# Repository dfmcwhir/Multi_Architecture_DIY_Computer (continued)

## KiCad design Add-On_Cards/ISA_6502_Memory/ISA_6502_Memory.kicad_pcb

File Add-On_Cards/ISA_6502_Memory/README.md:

# <h2> 6502 Memory expansion card</h2>
<p>New card that hasn't been built or tested yet. It is currently only planned to be used with the 6502_CPU_Rev2 card. It is possible that in the future other CPU cards can be adapted to use this card as well. When I designed this card, I went for maximum RAM, so consequently it has 16 banks of RAM and only the one bank of ROM selectable by the CPU. My thinking was that I have mass storage options for permanent storage, so I didn't need more ROM. That maybe fine, but I kind of wish I had designed it with more flexibility in mind. Maybe that will for the next revision. Maybe I want to add ROM banks for a cartridge like system for instance. </p>

<p>To enable the memory card the address decoding PLD on the 6502_CPU_Rev2 needs to disable the on-board ROM and RAM (which in the PLD file means commenting out "Block A") and enabling the external memory card (which means uncommenting out "Block B" in the PLD file).</p>

<h2> Populating the memory card</h2>
<p>There is one socket for RAM that can be set via a jumper JP1 to be either an AS6C1008 or AS6C4008 chip. There are 2 ROM sockets for flexibility, but only one can be populated. Socket 2 (32pins), can be a SST39SF010 OR a OneROM can be put in socket 3 (28pins). The OneROM can be configured as either a 27512 (JP3 pins 1-2) or a 23C1000 (JP3 pins 2-3). A 27512 (and possibly other 28 pin ROMs) could also be used in the OneROM socket. The important thing to remember is that only one of the 2 sockets can be populated. Regardless of the which socket or what type of chip is used, only 32K of the ROM will be addressable by the CPU.</p>

<h2> RAM Bank Selection</h2>
<p>The card’s RAM range $0000–$7EFF is split in two:

* $0000–$0FFF: fixed. It’s always bank 0 of the RAM chip, whatever bank is selected, so zero page, the stack and the BIOS variables never disappear.
* $1000–$7EFF: the banked window (about 28K). Which bank you see is set by the bank register.

The bank register sits on the CPU board, in the interrupt GAL at $7FFE. Writing a value 0–15 there puts it on bus lines BA16–BA19. The card’s GAL passes those bits to the RAM chip’s top address lines (RA15–RA18), but only while the address is in the window. In the fixed area it forces them to 0.

Each bank is a 32K slice of the RAM chip: physical address = bank × $8000 + CPU address.

* AS6C4008 (512K): 16 banks (JP1 2–3).
* AS6C1008 (128K): 4 banks (JP1 1–2).

The $0000–$0FFF part of every slice except bank 0 is simply never reached. That’s the price of keeping the address calculation simple. </p>

<h2> Manual ROM bank selection </h2>
<p>The CPU can't select ROM banks, but different banks can be selected manually using jumpers. On the card, JP4 and JP5 choose which 32K image of the ROM chip appears at $8000–$FFFF. A 27SF512-style OneROM image holds 2 of them; the SST39SF010A and the MX23C1000 hold 4. Theoretically we could enable CPU switching of ROM banks by using bodge wires from JP4 and JP5 to the unused pins on the PLD and reprograming the PLD to use BA18-19 to control the ROM bank switching lines we added (RO15-16) instead of RA17-18. That would give us 4 banks of CPU switchable ROM at the expense of reducing us to 4 banks of RAM.</p>

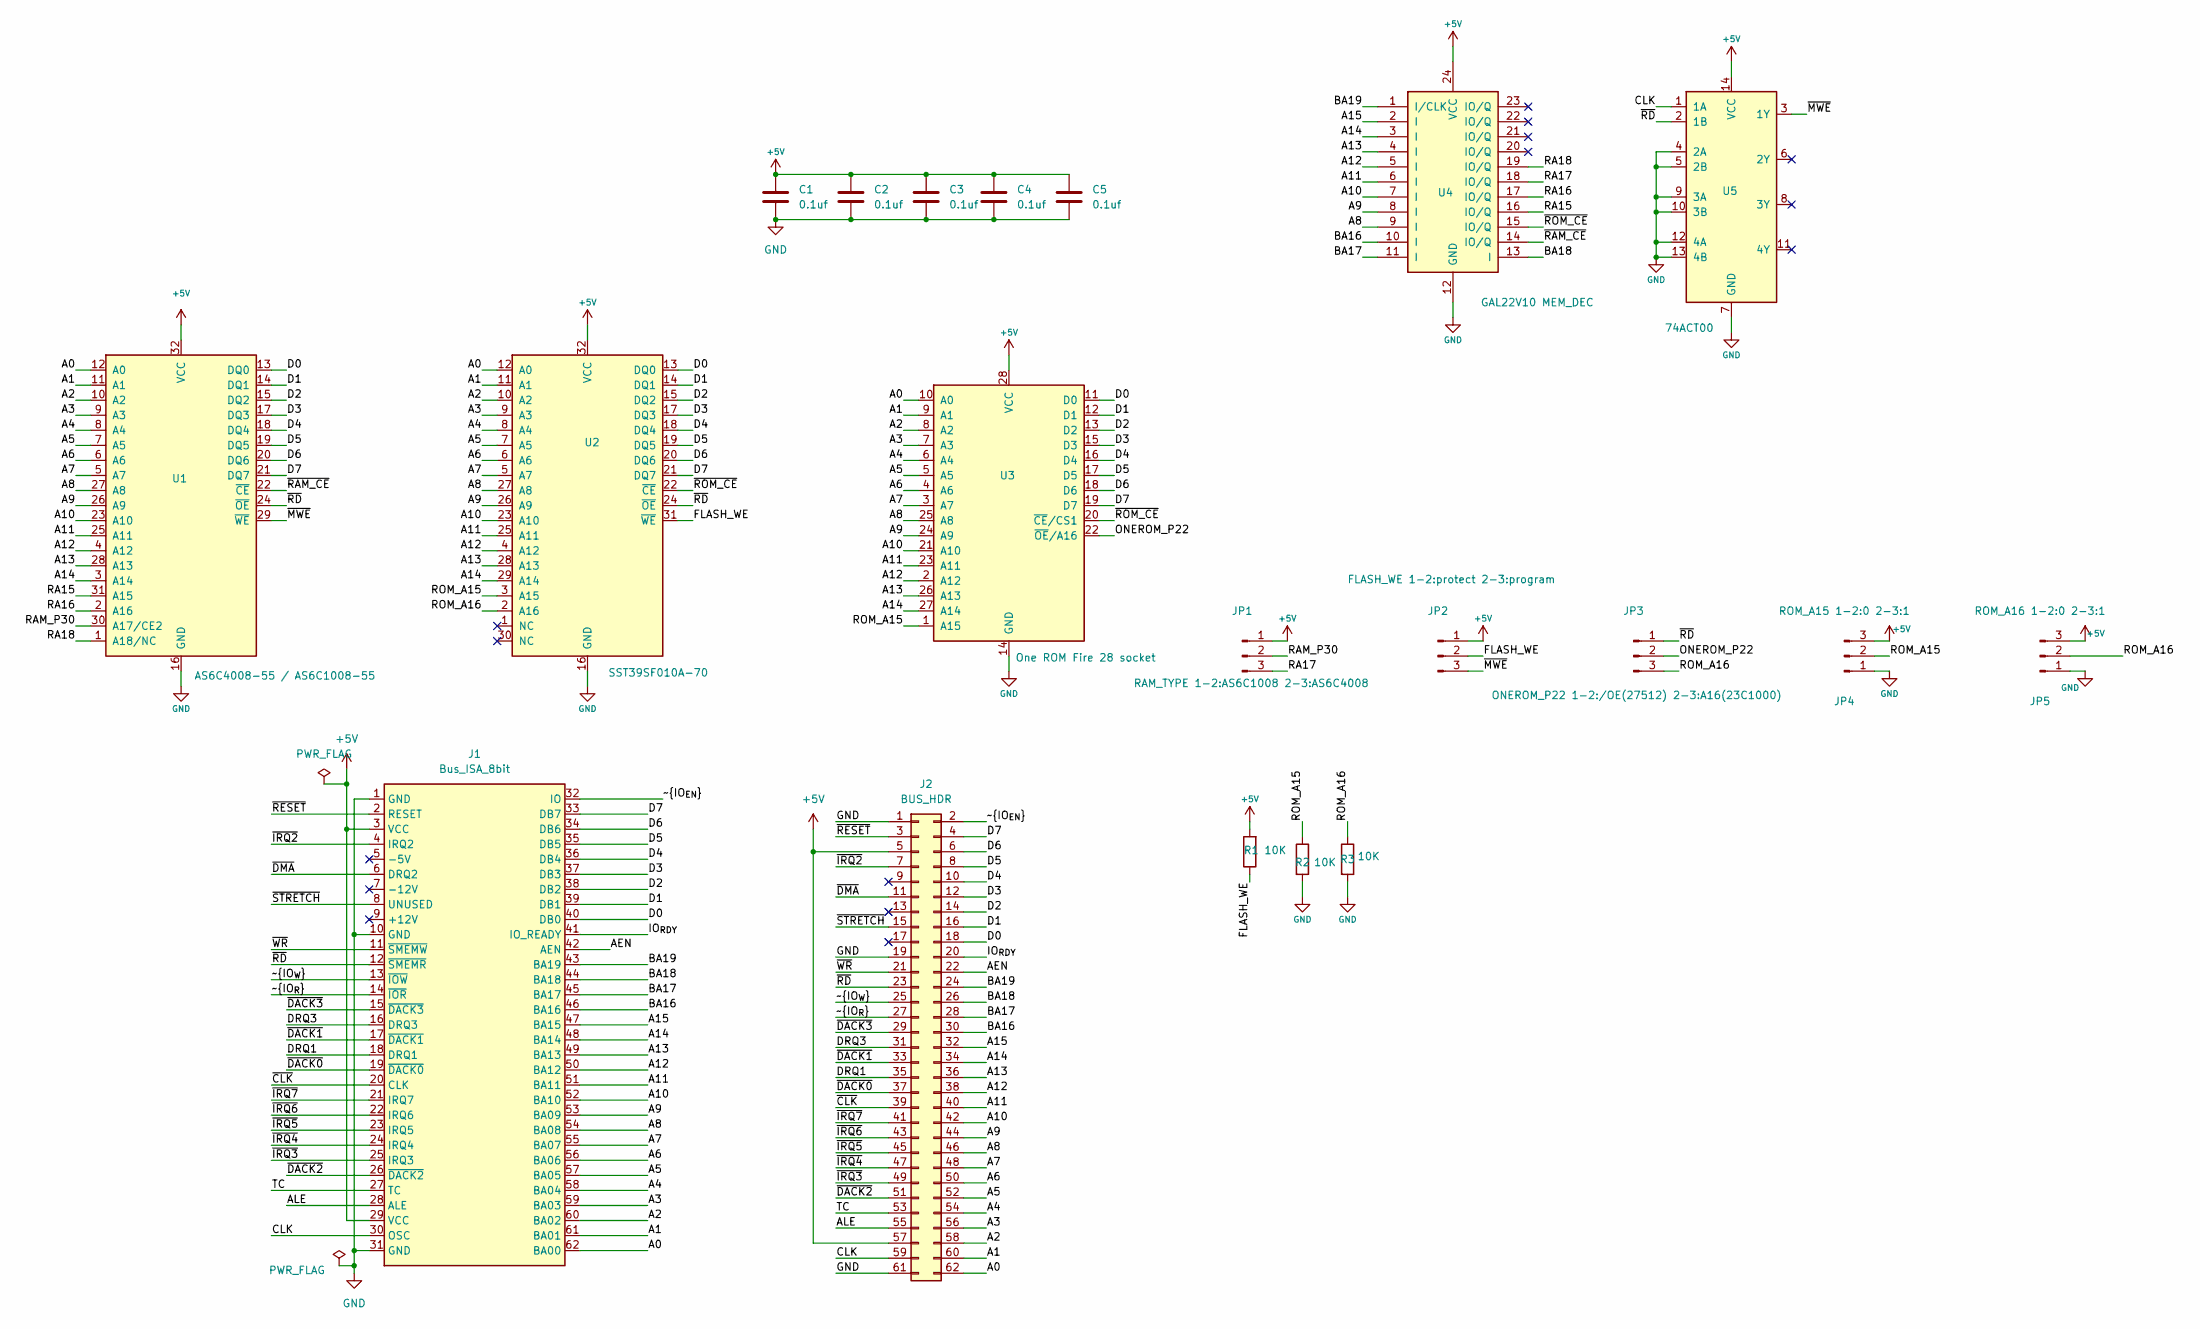
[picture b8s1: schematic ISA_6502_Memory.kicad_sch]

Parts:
C1, C2, C3, C4, C5: 0.1uf; C_Disc_D4.7mm_W2.5mm_P5.00mm
J1: Bus_ISA_8bit; BUS_8-bit_ISA
J2: BUS_HDR; PinHeader_2x31_P2.54mm_Vertical
JP1: RAM_TYPE 1-2:AS6C1008 2-3:AS6C4008; PinHeader_1x03_P2.54mm_Vertical
JP2: FLASH_WE 1-2:protect 2-3:program; PinHeader_1x03_P2.54mm_Vertical
JP3: ONEROM_P22 1-2:/OE(27512) 2-3:A16(23C1000); PinHeader_1x03_P2.54mm_Vertical
JP4: ROM_A15 1-2:0 2-3:1; PinHeader_1x03_P2.54mm_Vertical
JP5: ROM_A16 1-2:0 2-3:1; PinHeader_1x03_P2.54mm_Vertical
R1, R2, R3: 10K; R_Axial_DIN0207_L6.3mm_D2.5mm_P10.16mm_Horizontal
U1: AS6C4008-55 / AS6C1008-55; DIP-32_W15.24mm_Socket
U2: SST39SF010A-70; DIP-32_W15.24mm_Socket
U3: One ROM Fire 28 socket; DIP-28_W15.24mm_Socket
U4: GAL22V10 MEM_DEC; DIP-24_W7.62mm
U5: 74ACT00; DIP-14_W7.62mm

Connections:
+5V: C1.1, C2.1, C3.1, C4.1, C5.1, J1.3 (VCC), J1.29 (VCC), J2.5, J2.57, JP1.1, JP2.1, JP4.3, JP5.3, R1.2, U1.32 (VCC), U2.32 (VCC), U3.28 (VCC), U4.24 (VCC), U5.14 (VCC)
/A0: J1.62 (BA00), J2.62, U1.12 (A0), U2.12 (A0), U3.10 (A0)
/A1: J1.61 (BA01), J2.60, U1.11 (A1), U2.11 (A1), U3.9 (A1)
/A2: J1.60 (BA02), J2.58, U1.10 (A2), U2.10 (A2), U3.8 (A2)
/A3: J1.59 (BA03), J2.56, U1.9 (A3), U2.9 (A3), U3.7 (A3)
/A4: J1.58 (BA04), J2.54, U1.8 (A4), U2.8 (A4), U3.6 (A4)
/A5: J1.57 (BA05), J2.52, U1.7 (A5), U2.7 (A5), U3.5 (A5)
/A6: J1.56 (BA06), J2.50, U1.6 (A6), U2.6 (A6), U3.4 (A6)
/A7: J1.55 (BA07), J2.48, U1.5 (A7), U2.5 (A7), U3.3 (A7)
/A8: J1.54 (BA08), J2.46, U1.27 (A8), U2.27 (A8), U3.25 (A8), U4.9 (I)
/A9: J1.53 (BA09), J2.44, U1.26 (A9), U2.26 (A9), U3.24 (A9), U4.8 (I)
/A10: J1.52 (BA10), J2.42, U1.23 (A10), U2.23 (A10), U3.21 (A10), U4.7 (I)
/A11: J1.51 (BA11), J2.40, U1.25 (A11), U2.25 (A11), U3.23 (A11), U4.6 (I)
/A12: J1.50 (BA12), J2.38, U1.4 (A12), U2.4 (A12), U3.2 (A12), U4.5 (I)
/A13: J1.49 (BA13), J2.36, U1.28 (A13), U2.28 (A13), U3.26 (A13), U4.4 (I)
/A14: J1.48 (BA14), J2.34, U1.3 (A14), U2.29 (A14), U3.27 (A14), U4.3 (I)
/A15: J1.47 (BA15), J2.32, U4.2 (I)
/AEN: J1.42 (AEN), J2.22
/ALE: J1.28 (ALE), J2.55
/BA16: J1.46 (BA16), J2.30, U4.10 (I)
/BA17: J1.45 (BA17), J2.28, U4.11 (I)
/BA18: J1.44 (BA18), J2.26, U4.13 (I)
/BA19: J1.43 (BA19), J2.24, U4.1 (I/CLK)
/CLK: J1.30 (OSC), J2.59, U5.1 (1A)
/D0: J1.40 (DB0), J2.18, U1.13 (DQ0), U2.13 (DQ0), U3.11 (D0)
/D1: J1.39 (DB1), J2.16, U1.14 (DQ1), U2.14 (DQ1), U3.12 (D1)
/D2: J1.38 (DB2), J2.14, U1.15 (DQ2), U2.15 (DQ2), U3.13 (D2)
/D3: J1.37 (DB3), J2.12, U1.17 (DQ3), U2.17 (DQ3), U3.15 (D3)
/D4: J1.36 (DB4), J2.10, U1.18 (DQ4), U2.18 (DQ4), U3.16 (D4)
/D5: J1.35 (DB5), J2.8, U1.19 (DQ5), U2.19 (DQ5), U3.17 (D5)
/D6: J1.34 (DB6), J2.6, U1.20 (DQ6), U2.20 (DQ6), U3.18 (D6)
/D7: J1.33 (DB7), J2.4, U1.21 (DQ7), U2.21 (DQ7), U3.19 (D7)
/DRQ1: J1.18 (DRQ1), J2.35
/DRQ3: J1.16 (DRQ3), J2.31
/FLASH_WE: JP2.2, R1.1, U2.31 (~WE)
/IO_{RDY}: J1.41 (IO_READY), J2.20
/ONEROM_P22: JP3.2, U3.22 (~OE/A16)
/RA15: U1.31 (A15), U4.16 (IO/Q)
/RA16: U1.2 (A16), U4.17 (IO/Q)
/RA17: JP1.3, U4.18 (IO/Q)
/RA18: U1.1 (A18/NC), U4.19 (IO/Q)
/RAM_P30: JP1.2, U1.30 (A17/CE2)
/ROM_A15: JP4.2, R2.1, U2.3 (A15), U3.1 (A15)
/ROM_A16: JP3.3, JP5.2, R3.1, U2.2 (A16)
/TC: J1.27 (TC), J2.53
/~CLK: J1.20 (CLK), J2.39
/~DACK0: J1.19 (~DACK0), J2.37
/~DACK1: J1.17 (~DACK1), J2.33
/~DACK2: J1.26 (~DACK2), J2.51
/~DACK3: J1.15 (~DACK3), J2.29
/~DMA: J1.6 (DRQ2), J2.11
/~IO_{EN}: J1.32 (IO), J2.2
/~IO_{R}: J1.14 (~IOR), J2.27
/~IO_{W}: J1.13 (~IOW), J2.25
/~IRQ2: J1.4 (IRQ2), J2.7
/~IRQ3: J1.25 (IRQ3), J2.49
/~IRQ4: J1.24 (IRQ4), J2.47
/~IRQ5: J1.23 (IRQ5), J2.45
/~IRQ6: J1.22 (IRQ6), J2.43
/~IRQ7: J1.21 (IRQ7), J2.41
/~MWE: JP2.3, U1.29 (~WE), U5.3 (1Y)
/~RAM_CE: U1.22 (~CE), U4.14 (IO/Q)
/~RD: J1.12 (~SMEMR), J2.23, JP3.1, U1.24 (~OE), U2.24 (~OE), U5.2 (1B)
/~RESET: J1.2 (RESET), J2.3
/~ROM_CE: U2.22 (~CE), U3.20 (~CE/CS1), U4.15 (IO/Q)
/~STRETCH: J1.8 (UNUSED), J2.15
/~WR: J1.11 (~SMEMW), J2.21
GND: C1.2, C2.2, C3.2, C4.2, C5.2, J1.1 (GND), J1.10 (GND), J1.31 (GND), J2.1, J2.19, J2.61, JP4.1, JP5.1, R2.2, R3.2, U1.16 (GND), U2.16 (GND), U3.14 (GND), U4.12 (GND), U5.4 (2A), U5.5 (2B), U5.7 (GND), U5.9 (3A), U5.10 (3B), U5.12 (4A), U5.13 (4B)

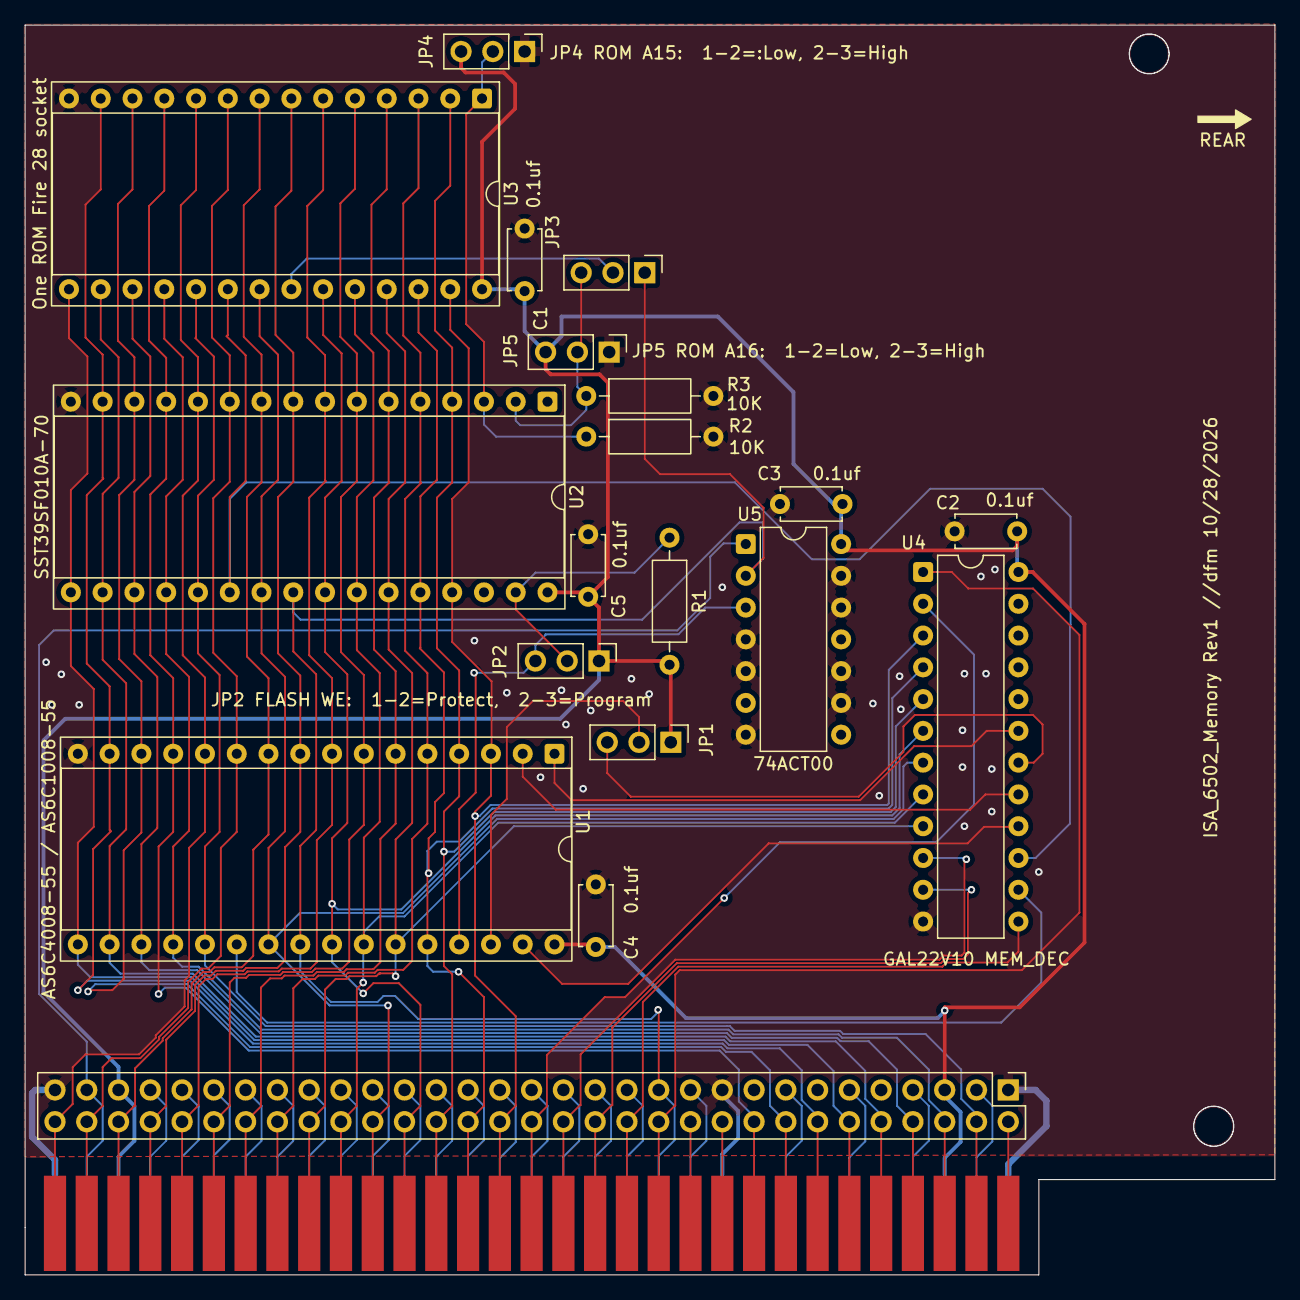
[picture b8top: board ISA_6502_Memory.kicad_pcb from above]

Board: 2 copper layers, 99.9 x 99.9 mm, 20 parts (0 on the bottom side), 68 nets.

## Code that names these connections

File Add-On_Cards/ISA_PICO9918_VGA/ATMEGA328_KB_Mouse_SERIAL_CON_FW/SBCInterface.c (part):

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// The display output of the original (8-bit, 4-bit and TWI display links and
// the ANSI interpreter) has been removed - the PICO9918 is the display now.
//
// Version 2: adds a PS/2 mouse on PC4 (clock) and PC0 (data).
//
// What it does
// ------------
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//
// ATmega328P pin use (DIP-28, 11.0592 MHz crystal)
// ------------------------------------------------
//   PB0-PB5  AVR bus D0-D5  (to '573 D inputs and '574 Q outputs)
//   PD6-PD7  AVR bus D6-D7
//   PB6-PB7  crystal
//   PC0      MOUSE DATA  (pull-up 4.7k-10k)   - was the optional /CTS input
//   PC1      KB clock    (pull-up)
//   PC2      KB data     (pull-up)
//   PC3      /RTS out
//   PC4      MOUSE CLOCK (pull-up 4.7k-10k)
//   PC5      KBAVAIL out -> GAL pin 14   (10k pull-down)
//   PC6      /RESET - keep it as reset (using it as I/O needs the RSTDISBL
//            fuse, which stops ISP programming)
//   PD0      RXD
//   PD1      TXD
//   PD2      INT0 <- /KBRD (GAL pin 17)  - byte acknowledge
//   PD3      <- DBUSY (GAL pin 22)       - 6502 has written a TX byte
//   PD4      /DOE  -> '574 /OE and GAL pin 23 (10k pull-up)
//   PD5      LE    -> '573 LE (10k pull-down)
//
// Handshakes
// ----------
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#include <stdint.h>

// ---------------------------------------------------------------- pins
#define KBAVAIL_BIT  PC5
#define RTS_BIT      PC3
#define KB_CLK_BIT   PC1
#define KB_DATA_BIT  PC2
#define MS_CLK_BIT   PC4
#define MS_DATA_BIT  PC0
#define DBUSY_BIT    PD3
#define DOE_BIT      PD4
#define LE_BIT       PD5

#define BUS_B_MASK   0x3F   // PB0-PB5 = D0-D5
#define BUS_D_MASK   0xC0   // PD6-PD7 = D6-D7

// ---------------------------------------------------------------- PS/2 devices
typedef struct
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		}
		else
		{
			d->writeActive = 0;                 // 11: device ack bit
			d->bitCount = 0;
			d->shift = 0;
		}
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	}
}

// Keyboard clock (PC1) and mouse clock (PC4) both raise PCINT1
ISR(PCINT1_vect)
{
	uint8_t pinc = PINC;
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	hostIn = hostOut = 0;
	txIn = txOut = 0;

	// AVR bus: inputs, no pull-ups (PB6/PB7 are the crystal)
	DDRB = 0x00;
	PORTB = 0x00;

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
	// Port D: /DOE high (set before enabling the output), LE low,
	// pull-up on the /KBRD input
	PORTD = (1 << DOE_BIT) | (1 << PD2);
	DDRD = (1 << PD1) | (1 << DOE_BIT) | (1 << LE_BIT);

	// Clear any DBUSY left set at power-up: hold /DOE low for a few clocks
	PORTD &= ~(1 << DOE_BIT);
	_delay_us(20);
	PORTD |= (1 << DOE_BIT);

	// PS/2 clocks: PC1 (keyboard) and PC4 (mouse) pin-change interrupts
	lastPinC = PINC;
	PCICR = 1 << PCIE1;
	PCMSK1 = (1 << PCINT9) | (1 << PCINT12);

	// INT0 (PD2, /KBRD) on rising edge = end of the 6502's read
	EICRA = (1 << ISC01) | (1 << ISC00);
	EIFR = 1 << INTF0;
	EIMSK = 1 << INT0;
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
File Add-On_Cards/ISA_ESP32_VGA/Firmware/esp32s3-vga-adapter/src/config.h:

// ESP32-S3 VGA / keyboard / mouse / sound adapter for a W65C02S computer.
// Pin map and build-time configuration.
//
// Board: ESP32-S3-DevKitC-1 (WROOM-1 N16R8 or N8R2 etc.). GPIO 33-37 are left
// free because octal-PSRAM modules use them. GPIO 19/20 are the native USB
// pins (USB host for keyboard/mouse). GPIO 43/44 stay as UART0 for upload and
// debug through the board's "UART" USB port.
#pragma once
#include <stdint.h>

// ---------------------------------------------------------------- 6502 bus
// All bus pins must be < 32 so one read of GPIO_IN_REG captures everything.
// D0..D7 must be consecutive GPIOs starting at PIN_D0.
#define PIN_D0        4     // D0..D7 = GPIO4..GPIO11 (via 74LVC8T245)
#define PIN_A0        12    // register select bit 0   (from GAL, open drain + 1k pull-up)
#define PIN_A1        13    // register select bit 1   (input)
#define PIN_RW        14    // R/W from CPU, 1 = read  (input)
#define PIN_NCS       15    // /CS for $7F18-$7F1B, decoded by the GAL, active low
#define PIN_PHI2      16    // PHI2 clock (input)
#define PIN_ACK       17    // to GAL ACK: 0 = hold RDY low while selected
#define PIN_IRQ       18    // to GAL IRQREQ: 1 = pull /IRQ low

// ---------------------------------------------------------------- VGA
// 2-bit-per-channel resistor DAC like FabGL (64 colours).
// Pixel byte format: 0b00RRGGBB.
#define PIN_VGA_B0    46
#define PIN_VGA_B1    45
#define PIN_VGA_G0    48
#define PIN_VGA_G1    47
#define PIN_VGA_R0    42
#define PIN_VGA_R1    41
#define PIN_VGA_HSYNC 39
#define PIN_VGA_VSYNC 40

// ---------------------------------------------------------------- PS/2
// Through a BSS138 4-channel bidirectional level shifter (5 V <-> 3.3 V).
#define PIN_KBD_CLK   1
#define PIN_KBD_DAT   2
#define PIN_MOUSE_CLK 21
#define PIN_MOUSE_DAT 3

// ---------------------------------------------------------------- Audio
// Sigma-delta output -> RC low-pass filter -> amplifier / line out.
#define PIN_AUDIO     38

// ---------------------------------------------------------------- Video timing
// 640x480 @ 60 Hz industry standard timing, negative sync polarity.
#define VGA_PCLK_HZ   25175000
#define VGA_H_RES     640
#define VGA_V_RES     480
#define VGA_HFP       16
#define VGA_HSYNC     96
#define VGA_HBP       48
#define VGA_VFP       10
#define VGA_VSYNC     2
#define VGA_VBP       33
#define VGA_BOUNCE_LINES 8      // lines per bounce buffer (480 must be a multiple)

// Text layer: 80x30 cells of 8x16 pixels.
#define TEXT_COLS     80
#define TEXT_ROWS     30

// Bitmap layer: 320x240, 1 byte per pixel, shown pixel-doubled.
#define GFX_W         320
#define GFX_H         240

#define NUM_SPRITES   16
#define NUM_PATTERNS  32
#define SPRITE_SIZE   16

// Any colour byte with bit 6 set is transparent (sprites, text background).
#define COLOR_TRANSPARENT 0x40

// Size of the 6502 -> video command FIFO (entries, power of two).
#define VIDEO_FIFO_SIZE 16384

// ---------------------------------------------------------------- Audio synth
#define AUDIO_SAMPLE_RATE 31250
#define AUDIO_VOICES      4

#define FW_VERSION_MAJOR 1
#define FW_VERSION_MINOR 0
